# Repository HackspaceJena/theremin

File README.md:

# ⚠️ Archived repository

This repository was moved to / Dieses Repository befindet sich nun unter:

🔗 https://git.kraut.space/Krautspace/theremin

Theremin
========

This project realizes a real Theremin (in contrast to our small [Light Theremin](https://github.com/HackspaceJena/light-theremin)).

The schematic and PCB files are created using [KiCAD](http://www.kicad-pcb.org/).

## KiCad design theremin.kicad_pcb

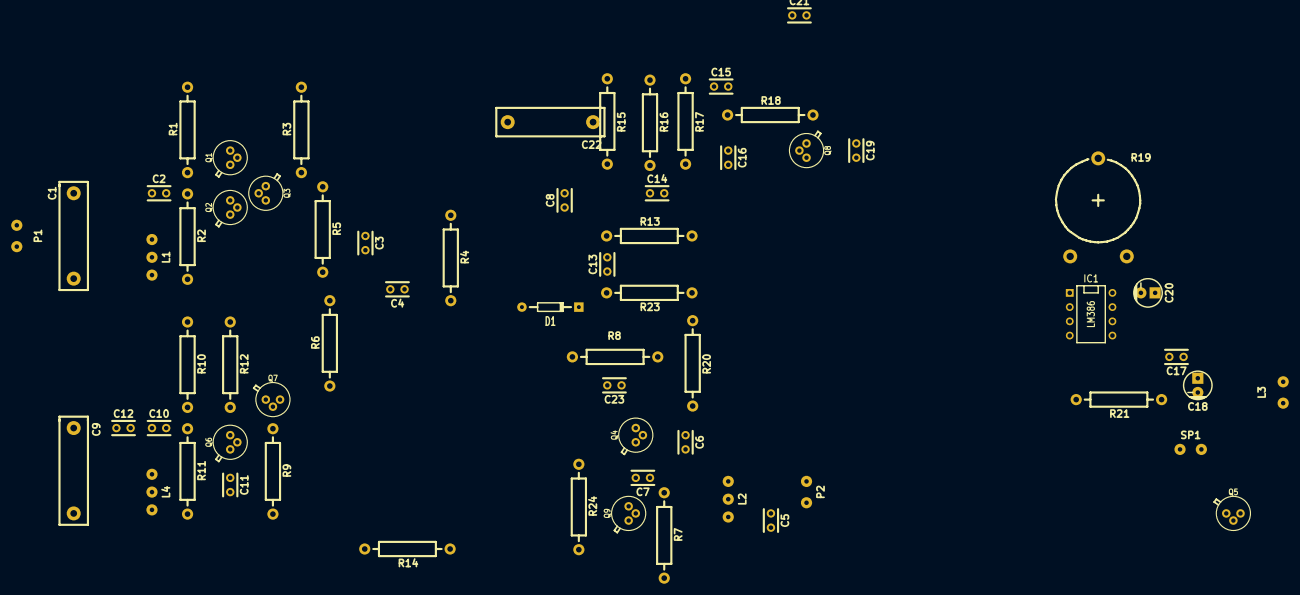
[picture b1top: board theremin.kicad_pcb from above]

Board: 2 copper layers, 64 parts (0 on the bottom side), 37 nets, no tracks yet.

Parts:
C1, C9, C22: 2-10pF; Capacitor18x5RM15
C2, C6, C10: 4.7pF; Capacitor4x3RM2.5
C3, C4, C7, C11: 10nF; Capacitor4x3RM2.5
C5: 2-10pF; Capacitor4x3RM2.5
C8: 51uF; Capacitor4x3RM2.5
C12: 10pF; Capacitor4x3RM2.5
C13, C19, C21: 100nF; Capacitor4x3RM2.5
C14: 220pF; Capacitor4x3RM2.5
C15: 560pF; Capacitor4x3RM2.5
C16: 33pF; Capacitor4x3RM2.5
C17: 47nF; Capacitor4x3RM2.5
C18: 250uF; Capacitor5x11RM2.5
C20: 10uF; Capacitor5x11RM2.5
C23: 1nF; Capacitor4x3RM2.5
D1: BAT54; Diode_DO-35_SOD27_Horizontal_RM10
IC1: LM386; DIP-8__300
L1: 31.6uH; SolderWirePad_3x_0-8mmDrill
L2: 56.3uH; SolderWirePad_3x_0-8mmDrill
L3: 4.7uH; SolderWirePad_2x_0-8mmDrill
L4: 5.3uH; SolderWirePad_3x_0-8mmDrill
P1: PITCH ANT; SolderWirePad_2x_0-8mmDrill
P2: VOLUME ANT; SolderWirePad_2x_0-8mmDrill
Q1, Q2, Q4, Q6, Q9: 2N2222; TO18EBC
Q3, Q5, Q7: PN3640; TO18EBC
Q8: PN5089; TO18EBC
R1, R2, R5, R6, R7, R10, R11, R13, R14: 100k; Resistor_Horizontal_RM15mm
R3, R4, R9, R18, R21: 3.3k; Resistor_Horizontal_RM15mm
R8: 1500; Resistor_Horizontal_RM15mm
R12: 1.5k; Resistor_Horizontal_RM15mm
R15, R16, R17: 49.9k; Resistor_Horizontal_RM15mm
R19: 10k; Potentiometer_Trimmer-Piher_PT15-V17-5_horizontal
R20: 330; Resistor_Horizontal_RM15mm
R23, R24: 470; Resistor_Horizontal_RM15mm
SP1: SPEAKER; SolderWirePad_2x_0-8mmDrill

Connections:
GND: C1.2, C4.2, C5.2, C8.2, C9.2, C12.2, C14.2, C16.2, C21.1, C22.2, IC1.4, L1.2, L2.2, L3.2, L4.2, P1.2, Q2.2, Q9.1, R2.2, R6.2, R7.2, R9.2, R11.2, R14.2, R18.2, R21.2, R24.2, SP1.2
unnamed: C1.1, C2.1, L1.1, P1.1
unnamed: C2.2, Q1.2, R1.2, R2.1
unnamed: C3.1, Q1.1, Q2.3, Q3.2
unnamed: C3.2, L1.3
unnamed: C4.1, D1.1, R4.2
unnamed: C5.1, P2.2
unnamed: C6.1, Q4.2, R5.2, R6.1
unnamed: C6.2, L2.1, P2.1
unnamed: C7.1, L2.3
unnamed: C7.2, Q4.1, Q5.2, R7.1
unnamed: C9.1, C10.1, C12.1, L4.1
unnamed: C10.2, Q6.2, R10.2, R11.1
unnamed: C11.1, Q6.1, Q7.2, R9.1
unnamed: C11.2, L4.3
unnamed: C13.1, Q9.3, R23.2
unnamed: C13.2, R13.2, R14.1, R15.2
unnamed: C14.1, R15.1, R16.2
unnamed: C15.1, C19.1, Q8.1, R18.1
unnamed: C15.2, R16.1, R17.2
unnamed: C16.1, Q8.2, R17.1
unnamed: C17.1, C18.1, IC1.5
unnamed: C17.2, R21.1
unnamed: C18.2, SP1.1
unnamed: C19.2, IC1.3
unnamed: C20.1, R19.2, R19.3
unnamed: C20.2, IC1.8
unnamed: C21.2, IC1.2
unnamed: C8.1, C22.1, D1.2, L3.1, Q5.3
unnamed: C23.1, R20.1
unnamed: IC1.1, R19.1
unnamed: Q2.1, R4.1
unnamed: Q3.1, R3.2
unnamed: Q3.3, Q7.3, Q9.2, R24.1
unnamed: Q5.1, R8.2, R20.2
unnamed: Q7.1, R12.2
VCC: C23.2, IC1.6, Q1.3, Q4.3, Q6.3, Q8.3, R1.1, R3.1, R5.1, R8.1, R10.1, R12.1, R13.1, R23.1

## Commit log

2014-07-14 Addded schematic file and special parts library.
2014-07-14 Added links in README.md
2014-08-11 Completed schematic. Started PCB layout.
2014-08-12 Corrected some footprints in PCB.
2024-01-26 archive repo
